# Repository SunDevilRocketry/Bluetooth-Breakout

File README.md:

# Bluetooth-Breakout
STM Bluetooth board with chip and antenna based around the STMWB50

Antenna: W3008

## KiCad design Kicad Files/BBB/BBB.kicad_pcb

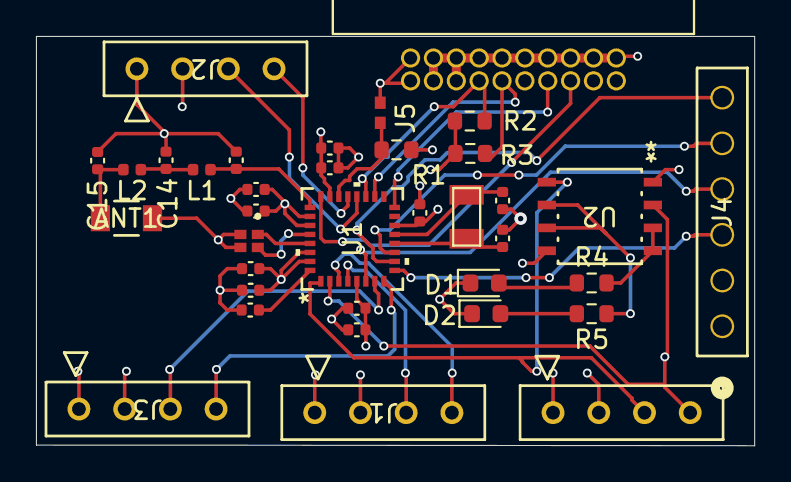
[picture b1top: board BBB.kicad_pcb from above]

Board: 4 copper layers, 39.9 x 22.7 mm, 36 parts (0 on the bottom side), 31 nets.

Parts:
ANT1: W3008; ANT_W3008_PUL
C1, C3, C4, C5, C6, C8, C10: 100n; C_0402_1005Metric
C2: 470n; C_0402_1005Metric
C7, C9: 1u; C_0402_1005Metric
C11, C12: 6p; C_0402_1005Metric
C13: 1.5p; C_0402_1005Metric
C14: 1.8p; C_0402_1005Metric
C15: 1p; C_0402_1005Metric
D1, D2: LED; LED_0603_1608Metric
J1, J2, J3, J6: PPTC041LFBN-RC; CONN_PPTC041LFBN-RC_SUL
J4: PPTC061LFBN-RC; CONN6_061LFBN-RC_SUL
J5: Jumper_NO; Jumper-NO
L1, L2: 3.3n; L_0402_1005Metric
P1: 3220-20-0200-00
R1: 10k; R_0603_1608Metric
R2, R3: 100k; R_0603_1608Metric
R4, R5: RES_0603; R_0603_1608Metric
U1: STM32WBA50KGU6; UFQFPN-32_1_STM
U2: LM393F-GE2; SOP8_ROM
Y1: ABS07AIG-32.768KHZ-T; XTAL320X150X90
Y2: 416F32022CKR; XTAL_416F32022CKR

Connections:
3.3V: C1.1, C2.1, C3.1, C4.1, C5.1, C6.1, C7.1, C8.1, C9.1, J1.2, J2.2, J3.2, J4.2, J5.2 (B), J6.2, P1.1, P1.2, R2.2, R3.2, U1.5 (VDD), U1.14 (VDD), U1.23 (VDDA), U1.26 (VDDHPA), U1.27 (VDDRF), U1.30 (VDDRFPA), U1.31 (VDD), U2.8 (VCC)
BOOT0: J5.1 (A), R1.1, U1.22 (PH3-BOOT0)
GND: ANT1.2, C1.2, C2.2, C3.2, C4.2, C5.2, C6.2, C7.2, C8.2, C9.2, C10.2, C11.2, C12.2, C13.2, C14.2, C15.2, D1.1 (K), D2.1 (K), J1.1, J2.1, J3.1, J4.1, J6.1, P1.3, P1.4, P1.5, P1.6, P1.8, P1.10, P1.12, P1.14, P1.16, P1.18, P1.20, R1.2, U2.4 (VEE), Y2.2, Y2.3
GPIO_IN: J2.4, U1.21 (PB15)
GPIO_OUT: J2.3, U1.20 (PA12)
I2C_SCL: J1.3, U1.4 (PA6)
I2C_SDA: J1.4, U1.3 (PA7)
NRST: P1.15, U1.24 (NRST)
unnamed: ANT1.1, C15.1, L2.2
unnamed: C14.1, L1.2, L2.1
unnamed: D1.2 (A), R4.1
unnamed: D2.2 (A), R5.2
unnamed: R4.2, U2.1 (OUT1), U2.2 (-IN1)
unnamed: R5.1, U2.6 (-IN2), U2.7 (OUT2)
OSC32_IN: C11.1, U1.13 (PC14-OSC32_IN), Y1.1
OSC32_OUT: C12.1, U1.12 (PC15-OSC32_OUT), Y1.2
OSC_IN: U1.29 (OSC_IN), Y2.1
OSC_OUT: U1.28 (OSC_OUT), Y2.4
RF: C13.1, L1.1, U1.25 (RF)
SPI_MISO: J4.6, U1.10 (PB9)
SPI_MOSI: J4.5, U1.11 (PB8)
SPI_NSS: J4.4, U1.6 (PA5)
SPI_SCK: J4.3, U1.9 (PA0)
SWCLK: P1.9, R3.1, U1.18 (PA14)
SWDIO: P1.7, R2.1, U1.19 (PA13)
SWO: P1.13, U1.16 (PB3)
UART_RX: J3.4, U1.8 (PA1)
UART_TX: J3.3, U1.7 (PA2)
USART_RX: J6.4, U1.2 (PA8), U2.3 (+IN1)
USART_TX: J6.3, U1.1 (PB12), U2.5 (+IN2)
VCAP: C10.1, U1.32 (VCAP)

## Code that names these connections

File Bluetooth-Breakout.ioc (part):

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Mcu.Name=STM32WBA50KGUx
Mcu.Package=UFQFPN32
Mcu.UserName=STM32WBA50KGUx
PA0.Mode=Full_Duplex_Master
PA0.Signal=SPI3_SCK
PA1.Mode=Asynchronous
PA1.Signal=LPUART1_RX
PA12.Signal=GPIO_Output
PA13\ (JTMS/SWDIO).Mode=Trace_Asynchronous_SW
PA13\ (JTMS/SWDIO).Signal=DEBUG_JTMS-SWDIO
PA14\ (JTCK/SWCLK).Mode=Trace_Asynchronous_SW
PA14\ (JTCK/SWCLK).Signal=DEBUG_JTCK-SWCLK
PA2.Mode=Asynchronous
PA2.Signal=LPUART1_TX
PA5.Mode=NSS_Signal_Hard_Output
PA5.Signal=SPI3_NSS
PA6.Mode=I2C
PA6.Signal=I2C3_SCL
PA7.Mode=I2C
PA7.Signal=I2C3_SDA
PA8.Mode=Asynchronous
PA8.Signal=USART1_RX
PB12.Mode=Asynchronous
PB12.Signal=USART1_TX
PB15.Signal=GPIO_Input
PB3\ (JTDO/TRACESWO).Mode=Trace_Asynchronous_SW
PB3\ (JTDO/TRACESWO).Signal=DEBUG_JTDO-SWO
PB8.Mode=Full_Duplex_Master
PB8.Signal=SPI3_MOSI
PB9.Mode=Full_Duplex_Master
PB9.Signal=SPI3_MISO
PC14-OSC32_IN.Mode=LSE-External-Oscillator
PC14-OSC32_IN.Signal=RCC_OSC32_IN
PC15-OSC32_OUT.Mode=LSE-External-Oscillator
PC15-OSC32_OUT.Signal=RCC_OSC32_OUT
RCC.HSESYSFreq_VALUE=16000000
RCC.HSE_VALUE=16000000
RCC.SYSCLKFreq_VALUE=16000000
board=custom

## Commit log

2025-03-05 Basics
    Decoupling Capacitors, HSE OSC, LSE OSC, etc. Basic board parts
2025-03-05 added W3008 bluetooth antenna schematic
2025-03-05 Ordering
    Added labeling to the BBB
2025-03-05 Antenna
    Added W3008 antenna to BBB schematic
2025-03-25 BBB Board
    Designed basic breakout board for the STMWBA chip
